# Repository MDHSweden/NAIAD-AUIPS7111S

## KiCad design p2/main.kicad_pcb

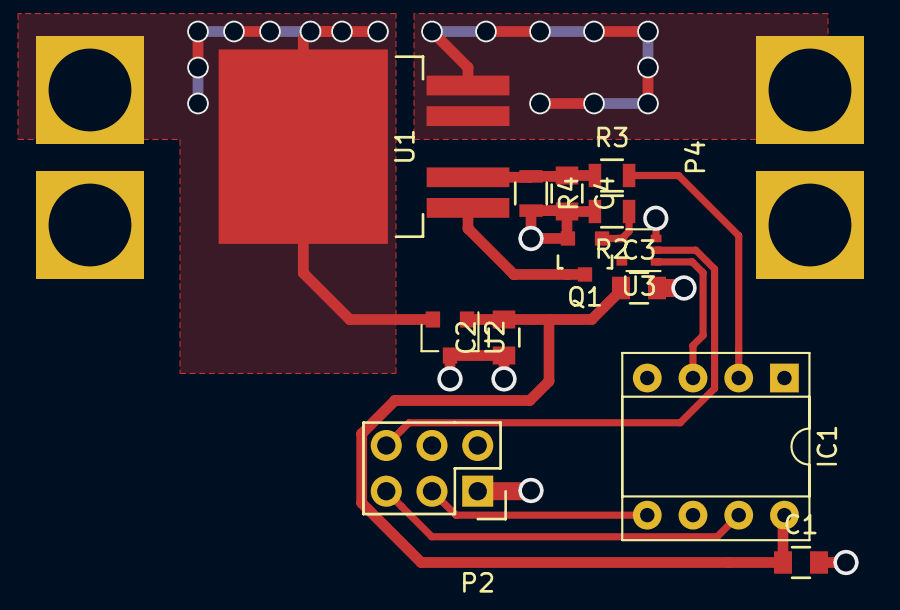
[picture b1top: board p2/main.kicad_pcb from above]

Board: 2 copper layers, 15 parts (0 on the bottom side), 12 nets.

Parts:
C1, C2, C3: 10uF; C_0805
C4: C; C_0805
IC1: ATTINY45-P; DIP-8_W7.62mm_Socket
P1, P4: CONN_XT60; XT60
P2: CONN_02X03; Socket_Strip_Straight_2x03
Q1: BSS138; SOT-23
R2: 4.7k; R_0805
R3: 10k; R_0805
R4: 3.3k; R_0805
U1: AUIPS7111S; TO-263-!3
U2: LM3480-5.0; SOT-23
U3: 74LVC1G08; SOT-353

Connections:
+5V: C1.1, C2.2, C3.1, IC1.8, U2.1, U3.5
/ENB: P2.6, U3.2
/IN: Q1.3, U1.1
/Ifb: C4.1, R3.1, R4.1, U1.2
/Out: P4.2, U1.4, U1.5
/SCL: IC1.7, P2.5
/SDA: IC1.5, P2.3
GND: C1.2, C2.1, C3.2, C4.2, IC1.4, P1.1, P2.1, P4.1, Q1.2, R2.2, R4.2, U2.3, U3.3
unnamed: IC1.2, R3.2
unnamed: IC1.3, U3.1
unnamed: Q1.1, R2.1, U3.4
VCC: P1.2, U1.3, U2.2

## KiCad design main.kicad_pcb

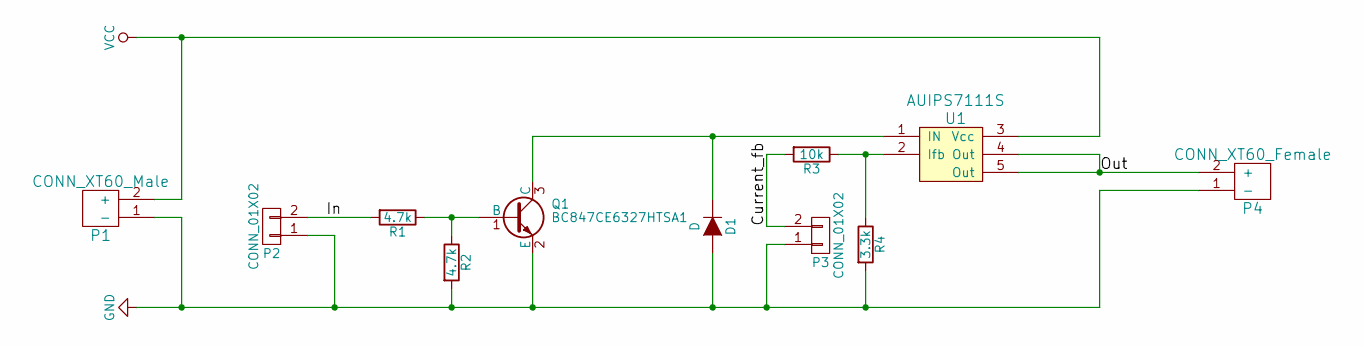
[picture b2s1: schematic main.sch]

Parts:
D1: D; Diode_DO-35_SOD27_Horizontal_RM10
P1: CONN_XT60_Male; CONN_XT60_Male1_Horizontal
P2, P3: CONN_01X02; Pin_Header_Straight_1x02
P4: CONN_XT60_Female; CONN_XT60_Female_Horizontal
Q1: BC847CE6327HTSA1; SOT-23
R1, R2: 4.7k; Resistor_Horizontal_RM7mm
R3: 10k; Resistor_Horizontal_RM7mm
R4: 3.3k; Resistor_Horizontal_RM7mm
U1: AUIPS7111S; TO-263-5Lead

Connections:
/Current_fb: P3.2, R3.2
/In: P2.2, R1.2
/Out: P4.2 (+), U1.4 (Out), U1.5 (Out)
GND: D1.2 (A), P1.1 (-), P2.1, P3.1, P4.1 (-), Q1.2 (E), R2.2, R4.2
unnamed: D1.1 (K), Q1.3 (C), U1.1 (IN)
unnamed: Q1.1 (B), R1.1, R2.1
unnamed: R3.1, R4.1, U1.2 (Ifb)
VCC: P1.2 (+), U1.3 (Vcc)

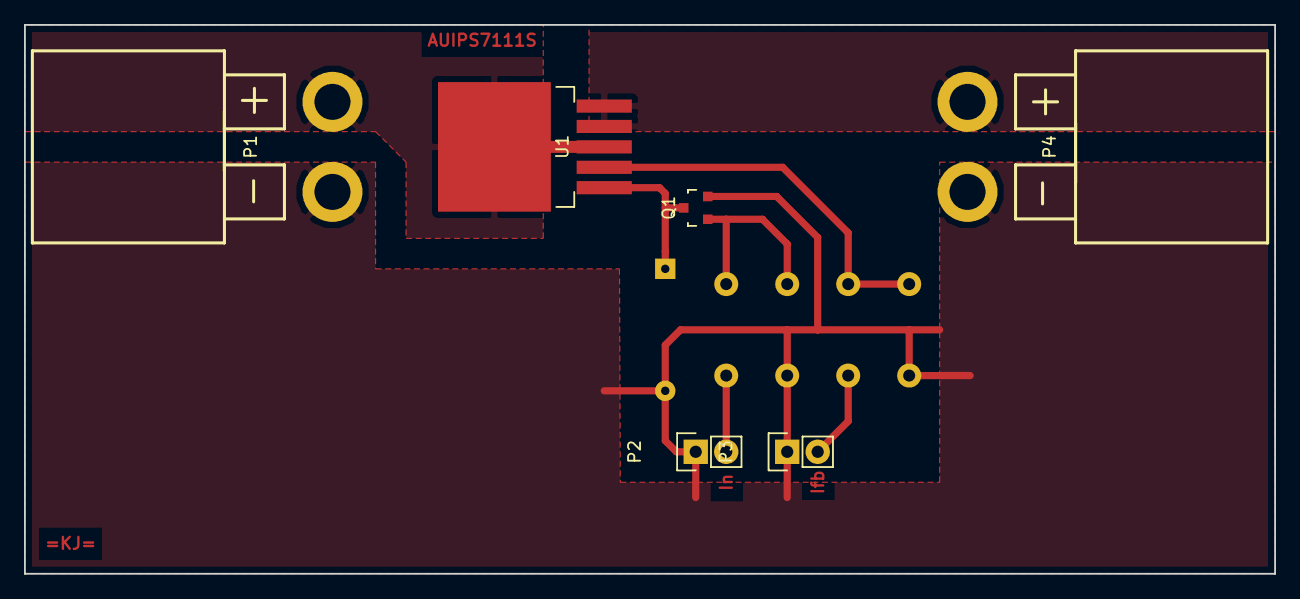
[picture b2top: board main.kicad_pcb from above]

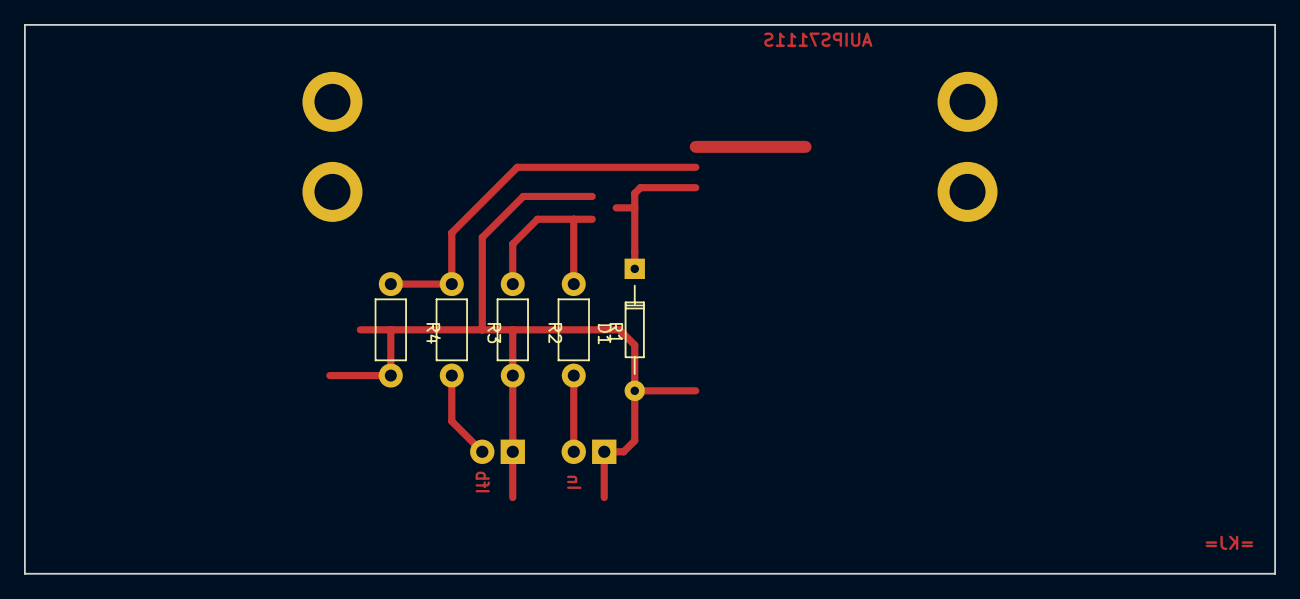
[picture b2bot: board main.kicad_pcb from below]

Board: 2 copper layers, 104.1 x 45.7 mm, 11 parts (5 on the bottom side), 8 nets.

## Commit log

2017-01-09 init
2017-01-09 test
